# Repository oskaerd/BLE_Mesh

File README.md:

*******Konfiguracja wizneta: 
	mac 	--->	0x00 0x08 0xdc 0xab 0xcd 0xef		
	ip 		--->	192.168.1.57							
	maska 	--->  	255.255.255.0							
	brama 	--->  	192.168.1.1
	
Konfiguracja polaczenia z serwerem:
	ip		--->	192.168.1.192
	socekt	--->	5000

Po dodaniu bibliotek do projektu w main() programu wywołujemy:
	
	config_wiznet();		
	config_server_param();
	
W pętli głównej programu:
	
	send_to_server();

*******Konfiguracja i2c

#include "user_sensor.h"

int main(void)
{
	double temperatura = 0;
	double cisnienie = 0;

	//Inicjalizacja Twi oraz czujnika
    twi_init();
	temp_init();

	while(1){
		temperatura = temp_odczyt();
		cisnienie = cisnienie_odczyt();
		nrf_delay_ms(100);
	}
}

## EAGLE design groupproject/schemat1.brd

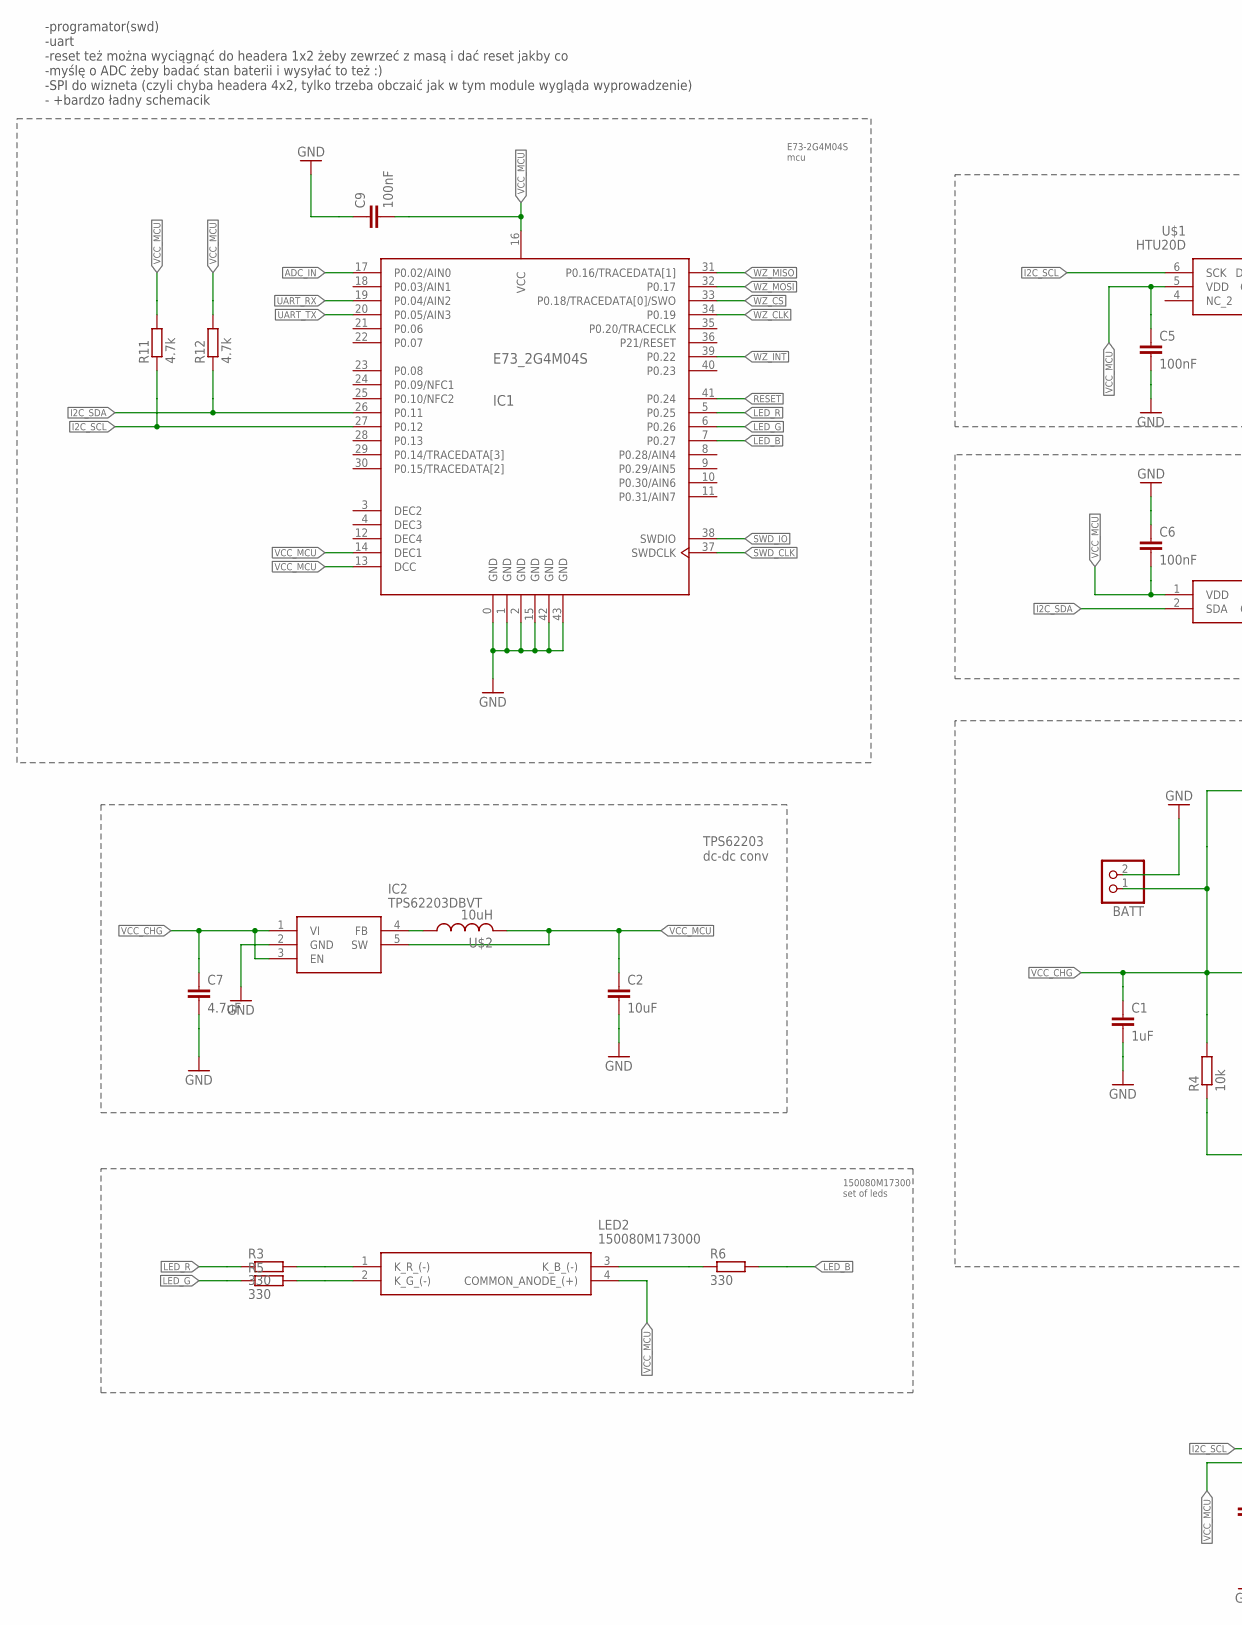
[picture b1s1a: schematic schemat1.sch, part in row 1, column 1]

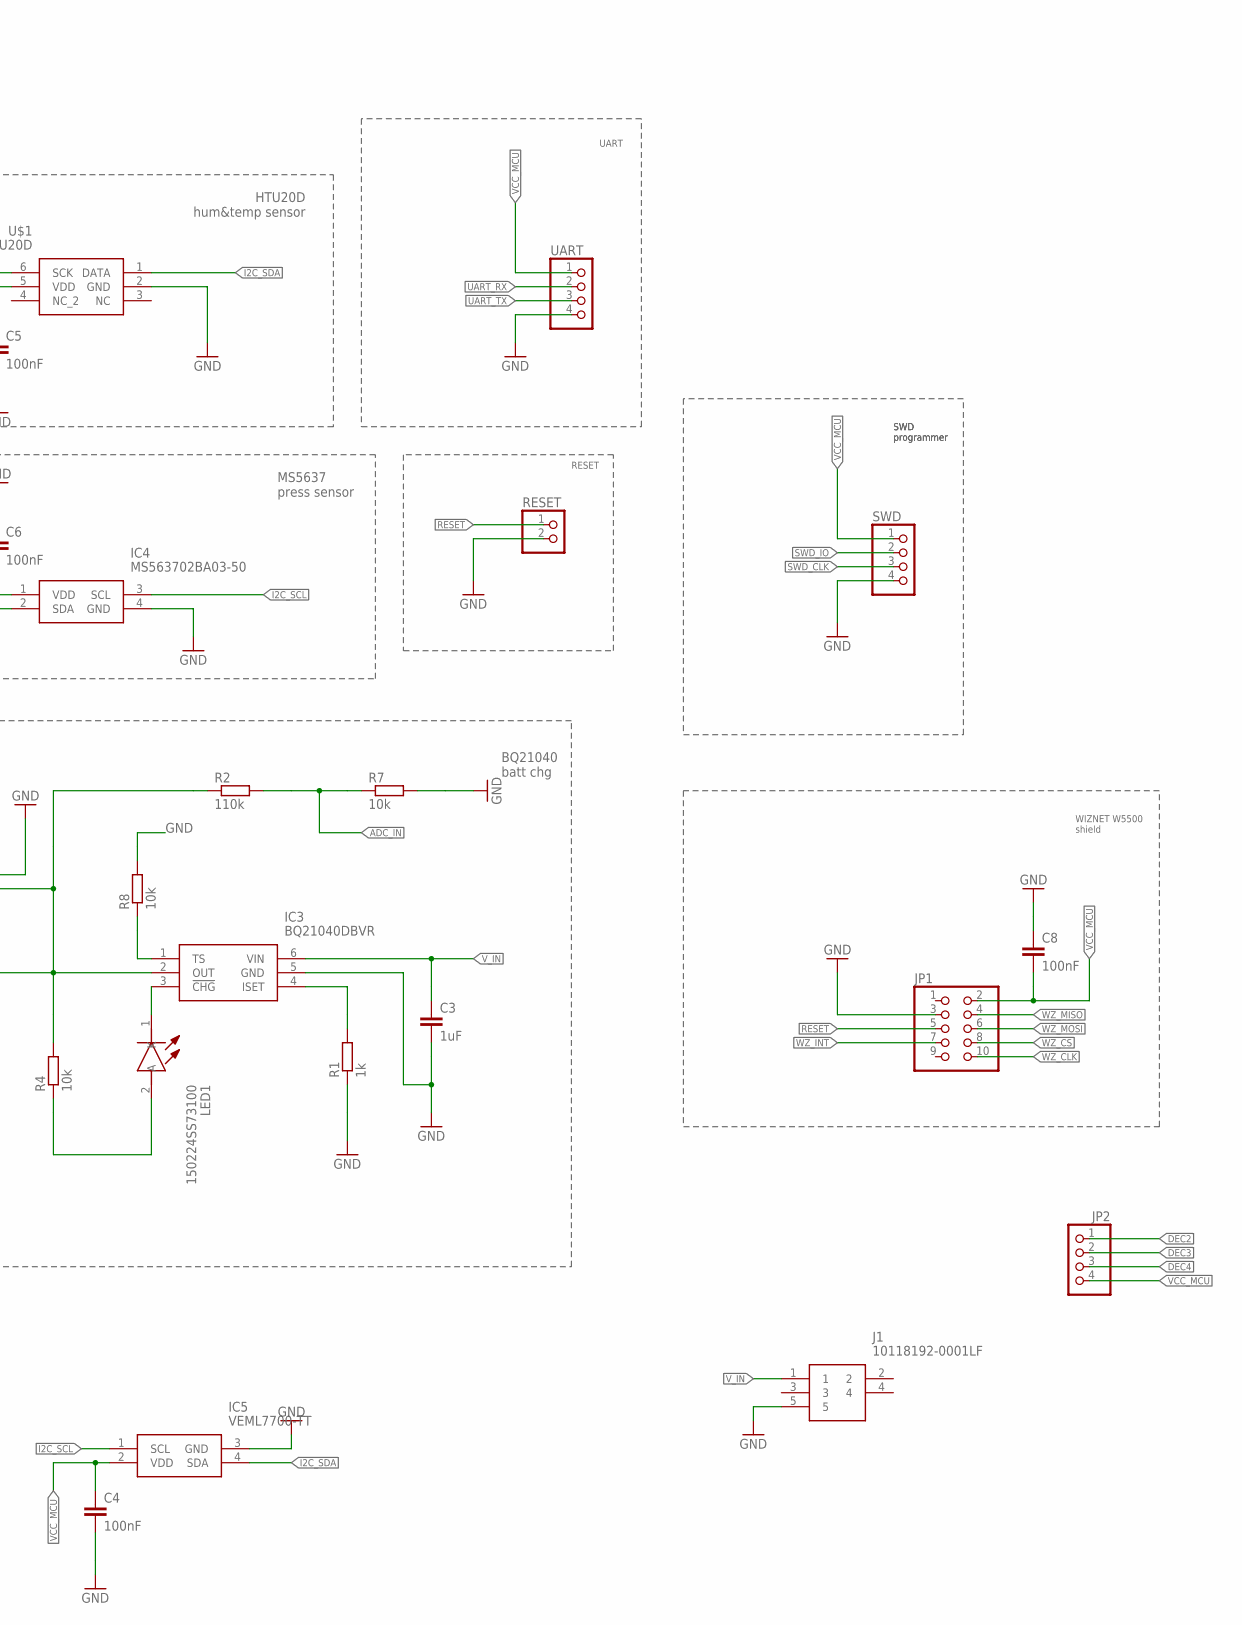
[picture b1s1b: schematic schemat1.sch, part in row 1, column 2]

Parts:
BATT: PINHD-1X2; 1X02
C1, C3: 1uF; C0603K
C2: 10uF; C0603K
C4, C5, C6, C8, C9: 100nF; C0603K
C7: 4.7uF; C0603K
IC1: E73_2G4M04S
IC2: TPS62203DBVT; SOT95P280X145-5N
IC3: BQ21040DBVR; SOT95P280X145-6N
IC4: MS563702BA03-50; MS5637_1
IC5: VEML7700-TT; VEML7700
J1: 10118192-0001LF
JP1: PINHD-2X5; 2X05
JP2: PINHD-1X4; 1X04
LED1: 150224SS73100; LEDM2314X131N
LED2: 150080M173000
R1: 1k; R0603
R2: 110k; R0603
R3, R5, R6: 330; R0603
R4, R7, R8: 10k; R0603
R11, R12: 4.7k; R0603
RESET: PINHD-1X2; 1X02
SWD: PINHD-1X4; 1X04
U$1: HTU20D; SON100P300X300X113-7N
U$2: 10uH; FB_BLM18PG121SN1D
UART: PINHD-1X4; 1X04

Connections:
ADC_IN: IC1.17 (P0.02/AIN0), R2.2, R7.1
DEC2: IC1.3 (DEC2), JP2.1
DEC3: IC1.4 (DEC3), JP2.2
DEC4: IC1.12 (DEC4), JP2.3
GND: BATT.2, C1.2, C2.2, C3.2, C4.2, C5.2, C6.1, C7.2, C8.1, C9.1, IC1.0 (GND), IC1.1 (GND), IC1.2 (GND), IC1.15 (GND), IC1.42 (GND), IC1.43 (GND), IC2.2 (GND), IC3.5 (GND), IC4.4 (GND), IC5.3 (GND), J1.5, JP1.3, R1.1, R7.2, R8.2, RESET.2, SWD.4, U$1.2 (GND), UART.4
I2C_SCL: IC1.27 (P0.12), IC4.3 (SCL), IC5.1 (SCL), R11.1, U$1.6 (SCK)
I2C_SDA: IC1.26 (P0.11), IC4.2 (SDA), IC5.4 (SDA), R12.1, U$1.1 (DATA)
LED_B: IC1.7 (P0.27), R6.2
LED_G: IC1.6 (P0.26), R5.1
LED_R: IC1.5 (P0.25), R3.1
unnamed: IC3.3 (!CHG), LED1.1 (K)
unnamed: IC2.4 (FB), U$2.1
unnamed: LED1.2 (A), R4.1
unnamed: LED2.3 (K_B_(-)), R6.1
unnamed: IC3.4 (ISET), R1.2
unnamed: LED2.2 (K_G_(-)), R5.2
unnamed: LED2.1 (K_R_(-)), R3.2
unnamed: IC3.1 (TS), R8.1
RESET: IC1.41 (P0.24), JP1.5, RESET.1
SWD_CLK: IC1.37 (SWDCLK), SWD.3
SWD_IO: IC1.38 (SWDIO), SWD.2
UART_RX: IC1.19 (P0.04/AIN2), UART.2
UART_TX: IC1.20 (P0.05/AIN3), UART.3
VCC_CHG: BATT.1, C1.1, C7.1, IC2.1 (VI), IC2.3 (EN), IC3.2 (OUT), R2.1, R4.2
VCC_MCU: C2.1, C4.1, C5.1, C6.2, C8.2, C9.2, IC1.13 (DCC), IC1.14 (DEC1), IC1.16 (VCC), IC2.5 (SW), IC4.1 (VDD), IC5.2 (VDD), JP1.2, JP2.4, LED2.4 (COMMON_ANODE_(+)), R11.2, R12.2, SWD.1, U$1.5 (VDD), U$2.2, UART.1
V_IN: C3.1, IC3.6 (VIN), J1.1
WZ_CLK: IC1.34 (P0.19), JP1.10
WZ_CS: IC1.33 (P0.18/TRACEDATA[0]/SWO), JP1.8
WZ_INT: IC1.39 (P0.22), JP1.7
WZ_MISO: IC1.31 (P0.16/TRACEDATA[1]), JP1.4
WZ_MOSI: IC1.32 (P0.17), JP1.6

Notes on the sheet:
HTU20D hum&temp sensor
MS5637 press sensor
TPS62203 dc-dc conv
BQ21040 batt chg
150080M17300 set of leds
-programator(swd) -uart -reset też można wyciągnąć do headera 1x2 żeby zewrzeć z masą i dać reset jakby co -myślę o ADC żeby badać stan baterii i wysyłać to też :) -SPI do wizneta (czyli chyba headera 4x2, tylko trzeba obczaić jak w tym module wygląda wyprowadzenie) - +bardzo ładny schemacik
RESET
SWD programmer
UART
WIZNET W5500 shield
E73-2G4M04S mcu

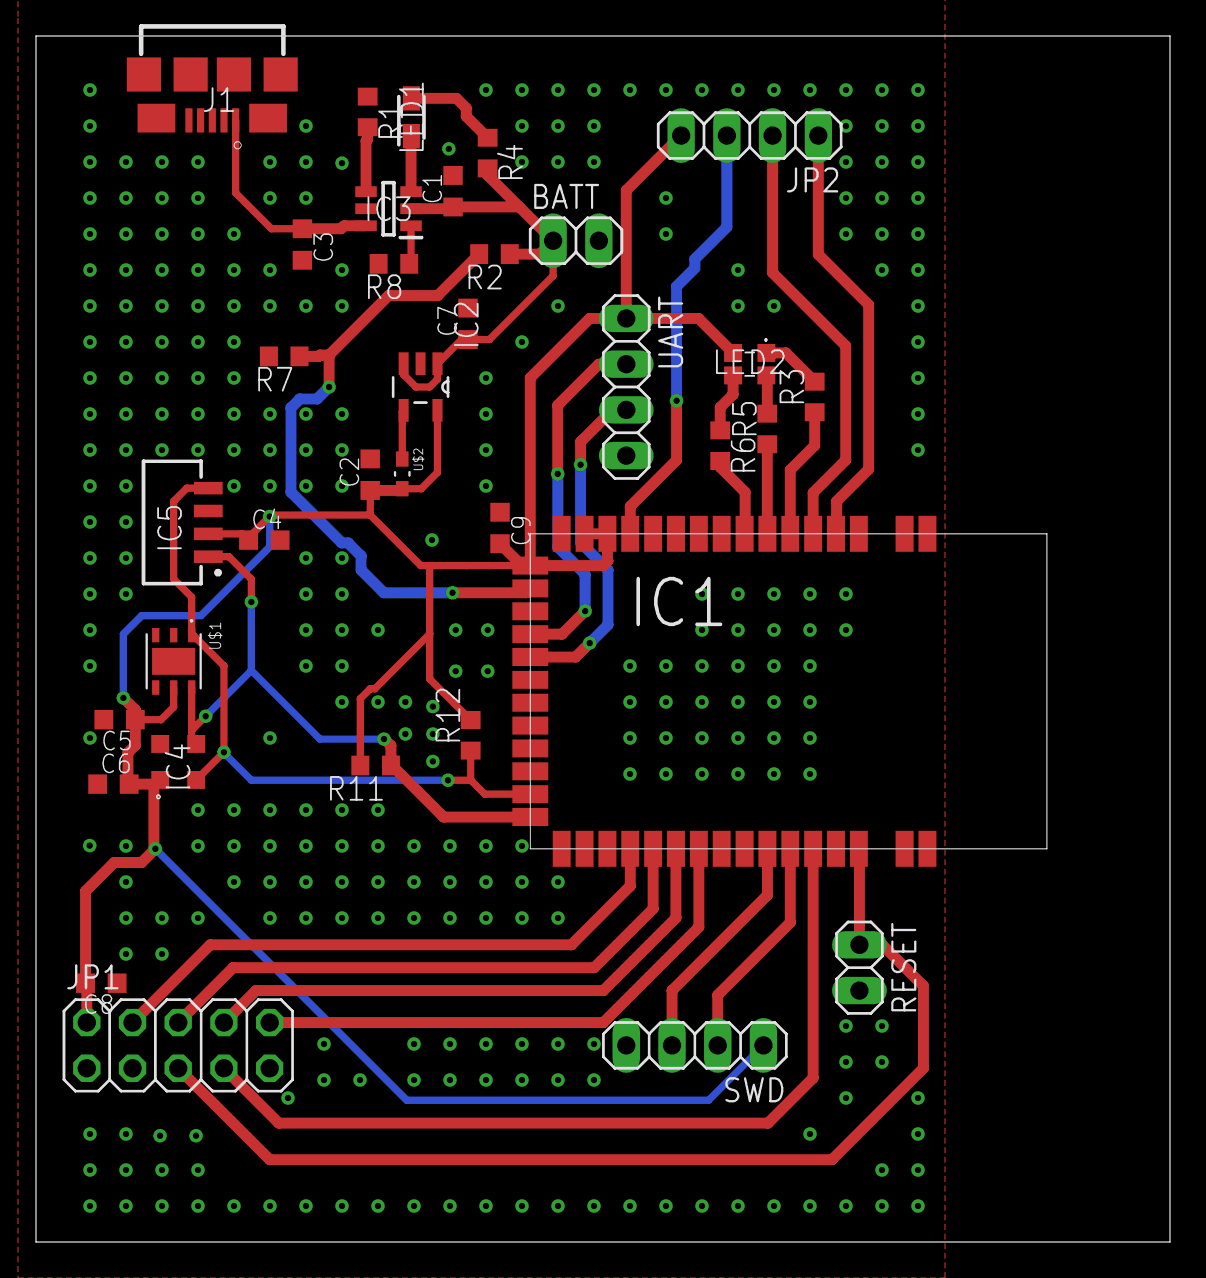
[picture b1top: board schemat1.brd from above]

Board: 2 copper layers, 63.0 x 67.0 mm, 35 parts (0 on the bottom side), 31 nets.

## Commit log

2019-01-28 resolved issue with bada data update
2019-01-28 implementing test-case scenario
2019-01-28 succesfull packing/unpacking data
2019-01-28 atexit handler
2019-01-28 inserting measurements into db
2019-01-28 succesfully adding measurements into db, dbreader utility created
2019-02-02 working on webapp
2019-02-03 abandoning webapp, moving to matplotlib
2019-02-03 creating db interface class
2019-02-03 remove database
2019-02-03 animated sin in tkinter window
2019-02-03 working display in tkinter
2019-02-09 init on firmware
2019-02-09 init on firmware branch
2019-02-09 modified gitignore
2019-02-09 modyfing segger project
2019-02-11 moved to 1.0.1 mesh sdk because i dont understand newer
2019-02-13 Ddoanie plikow do obslugi wizneta
2019-02-13 decided on sdk version
2019-02-13 Obsluga czujnika temp i cisnienia
2019-02-13 adding hw interface
2019-02-13 further changes
2019-02-13 before merge to firmware branch
2019-02-27 Add files via upload
    electric scheme and board scheme
